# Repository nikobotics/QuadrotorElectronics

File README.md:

# Quadrotor Electronics
Nikobotics Quadcopter Electronics Repository.

Using Altium Designer.

PCBs in this repository include:

- Electronic Flight Computer
- Power Distribution Board
- Peripheral Electronics and Indication Board

Plan to convert schematic into KiCAD upon redesign.

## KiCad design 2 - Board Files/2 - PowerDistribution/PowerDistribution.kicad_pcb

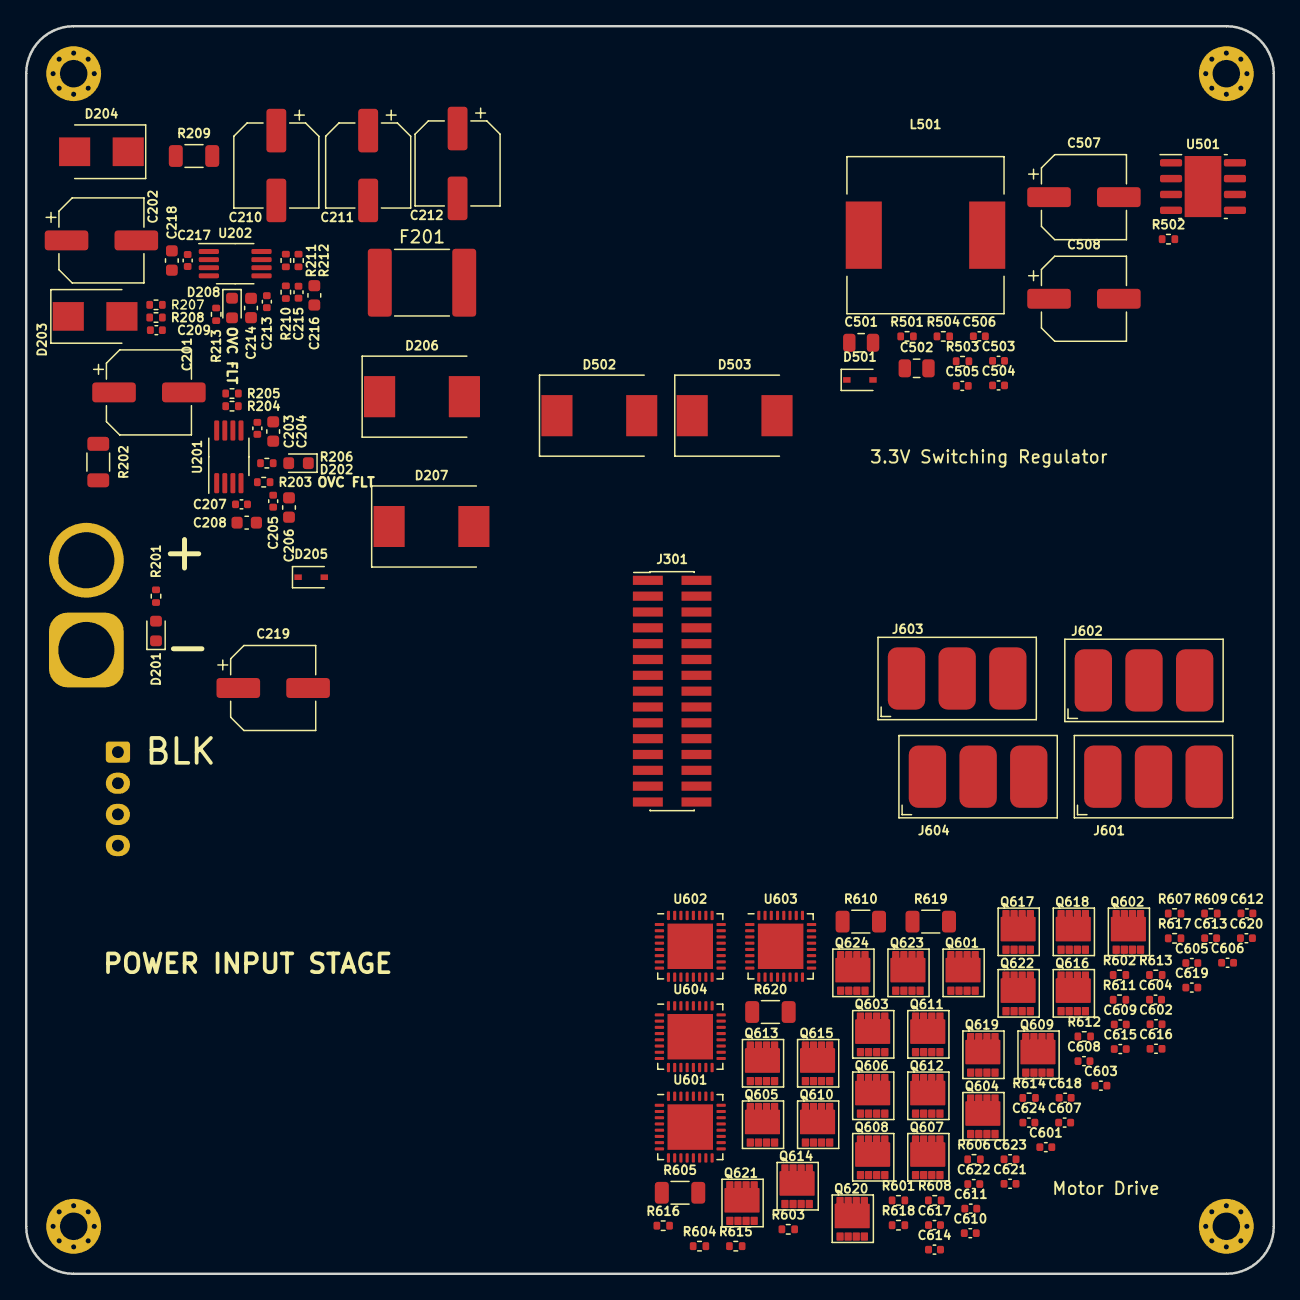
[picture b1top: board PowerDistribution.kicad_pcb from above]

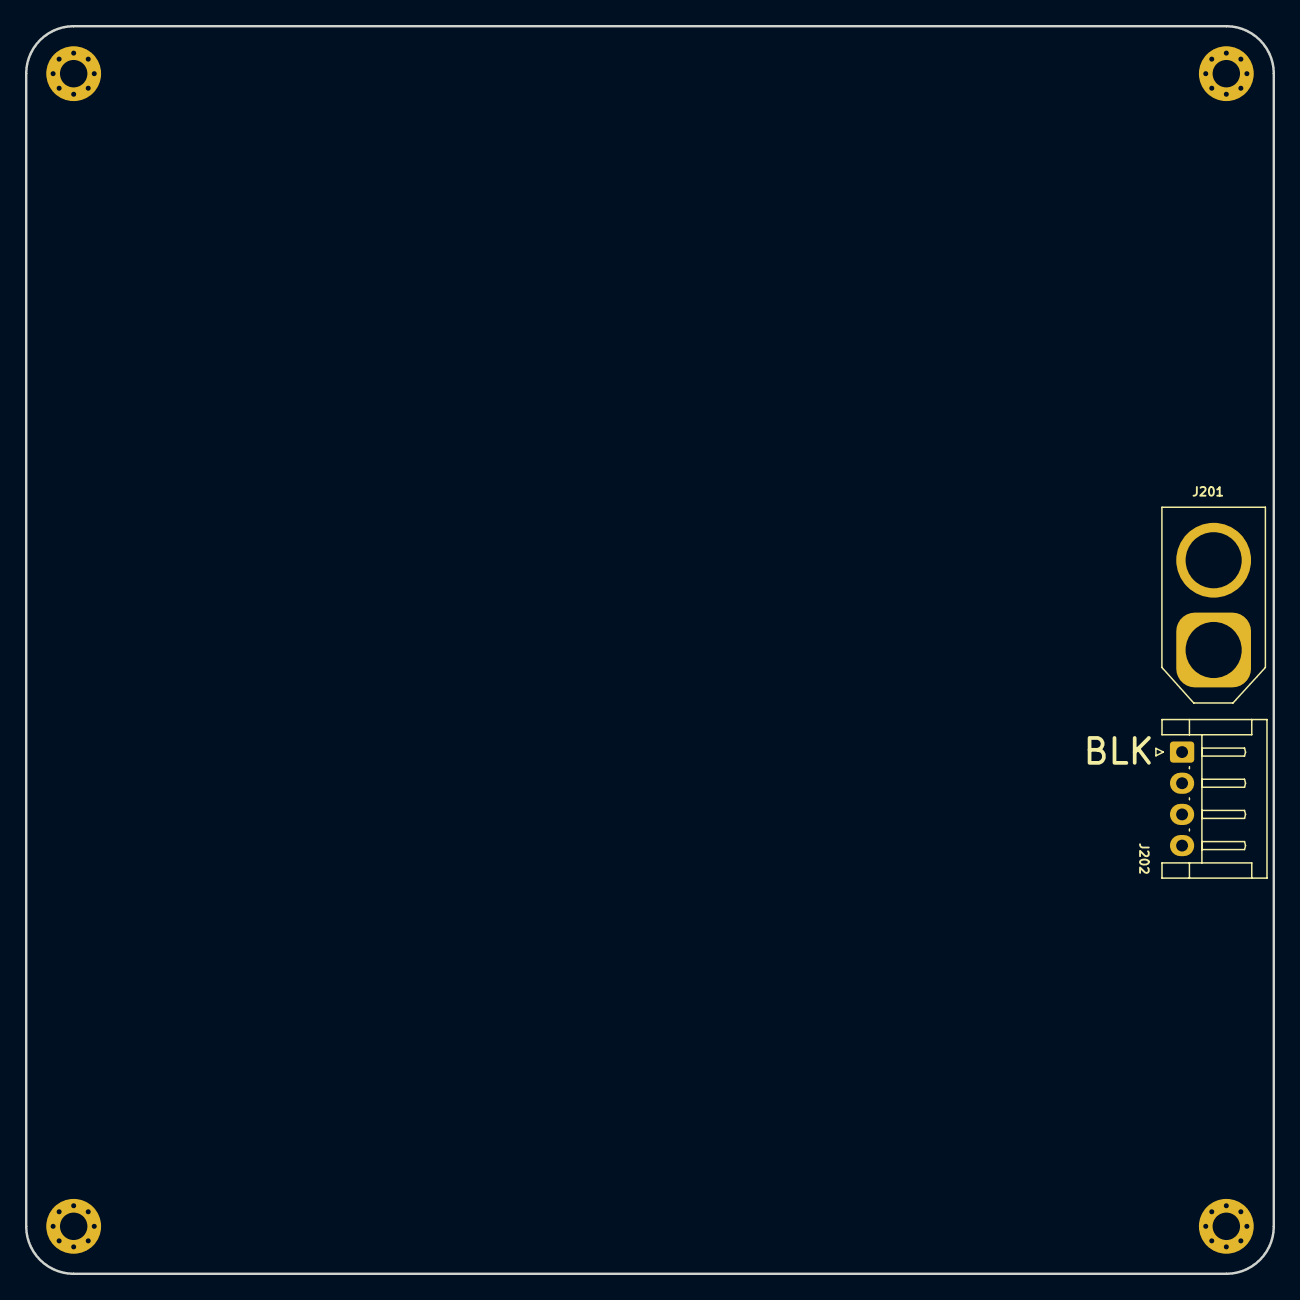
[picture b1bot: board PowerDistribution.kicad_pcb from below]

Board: 6 copper layers, 100.1 x 100.1 mm, 143 parts (2 on the bottom side), 99 nets, no tracks yet.

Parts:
C201, C202, C210, C211, C212, C507, C508: 10u; CP_Elec_6.3x5.4
C203, C205, C207, C213, C215, C217, C505: 10n; C_0402_1005Metric
C204, C206, C208, C214, C216, C218: 1u; C_0603_1608Metric
C209: 100n; C_0402_1005Metric
C219: 47u; CP_Elec_6.3x5.4
C501: 1u; C_0805_2012Metric
C502: 4u2; C_0805_2012Metric
C503, C504, C506, C601, C602, C603, C604, C605, C606, C607, C608, C609, C610, C611, C612, C613, C614, C615, C616, C617, C618, C619, C620, C621, C622, C623, C624: 0u1; C_0402_1005Metric
D201, D202, D208: LED; LED_0603_1608Metric
D203, D204: D; D_SMB
D205, D501: D_Zener; D_SOD-323
D206, D207: D_TVS; D_SMC
D502, D503: D; D_SMC
F201: Polyfuse; Fuse_2920_7451Metric
H101, H102, H103, H104: MountingHole; MountingHole_2.2mm_M2_Pad_Via
J201: Battery Input; AMASS_XT60-F_1x02_P7.20mm_Vertical
J202: Battery Balance Connector; JST_EH_S4B-EH_1x04_P2.50mm_Horizontal
J301: Conn_02x15_Counter_Clockwise; PinHeader_2x15_P1.27mm_Vertical_SMD
J601, J602, J603, J604: Conn_01x03_Female; MotorOutputPads
L501: 3u3; L_12x12mm_H4.5mm
Q601, Q602, Q603, Q604, Q605, Q606, Q607, Q608, Q609, Q610, Q611, Q612, Q613, Q614, Q615, Q616, Q617, Q618, Q619, Q620, Q621, Q622, Q623, Q624: Q_NMOS_GDS; 8-PowerVDFN
R201: R_Small_US; R_0402_1005Metric
R202, R605, R610, R619, R620: 1m, 3W; R_1206_3216Metric
R203, R210: 150R; R_0402_1005Metric
R204: 6k8; R_0402_1005Metric
R205: 3k3; R_0402_1005Metric
R206, R211, R213: 1k2; R_0402_1005Metric
R207: 22k; R_0402_1005Metric
R208: 82k; R_0402_1005Metric
R209: 22m, 3W; R_1206_3216Metric
R212: 9k1; R_0402_1005Metric
R501, R502: 1k; R_0402_1005Metric
R503: 68k1; R_0402_1005Metric
R504: 15k; R_0402_1005Metric
R601, R602, R603, R604, R606, R607, R608, R609, R611, R612, R613, R614, R615, R616, R617, R618: 4k7; R_0402_1005Metric
U201, U202: MAX40056F; MSOP-8_3x3mm_P0.65mm
U501: AOZ6605PI; SOIC-8-1EP_3.9x4.9mm_P1.27mm_EP2.95x4.9mm_Mask2.71x3.4mm
U601, U602, U603, U604: BD63003MUV; QFN-32-1EP_5x5mm_P0.5mm_EP3.65x3.65mm

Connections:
+3.3V: C507.1, C508.1, D501.1 (K), L501.2, R503.1
+3V3: C207.1, C208.1, C217.1, C218.1, R206.2, R213.2, U201.3 (VDD), U202.3 (VDD)
+BATT: C201.1, C202.1, C219.1, C601.1, C602.1, C604.1, C605.1, C606.1, C607.1, C608.1, C609.1, C610.1, C611.1, C613.1, C614.1, C615.1, C616.1, C617.1, C618.1, C619.1, C620.1, C622.1, C623.1, F201.1, Q601.2 (D), Q603.2 (D), Q605.2 (D), Q607.2 (D), Q609.2 (D), Q611.2 (D), Q613.2 (D), Q614.2 (D), Q617.2 (D), Q618.2 (D), Q621.2 (D), Q622.2 (D), R202.2, R603.1, R608.1, R613.1, R616.1, U201.1 (RS+), U601.4 (BRKB), U601.32 (VCC), U602.4 (BRKB), U602.32 (VCC), U603.4 (BRKB), U603.32 (VCC), U604.4 (BRKB), U604.32 (VCC)
/BATT_I_MON: C205.1, C206.1, R203.2
/BATT_V_MON: C209.1, D205.1 (K), R207.1, R208.2
/BatteryInput/BAT+_IN: J201.2, R201.2, R202.1, U201.8 (RS-)
/BatteryInput/BATT_SNS_CIP: R204.2, R205.1, U201.7 (CIP)
/BatteryInput/BATT_SNS_OUT: R203.1, U201.4 (OUT)
/BatteryInput/BATT_SNS_REF: C203.1, C204.1, R204.1, U201.5 (REF)
/BatteryInput/VDC_SNS_CIP: R211.2, R212.1, U202.7 (CIP)
/BatteryInput/VDC_SNS_IN: D204.1 (K), R209.1, U202.8 (RS-)
/BatteryInput/VDC_SNS_OUT: R210.1, U202.4 (OUT)
/BatteryInput/VDC_SNS_REF: C213.1, C214.1, R211.1, U202.5 (REF)
/ControlPower/SWITCH_SRC: C501.1, C502.1, D502.1 (K), D503.1 (K), U501.2 (EN), U501.3 (VIN)
/VDC_I_MON: C215.1, C216.1, R210.2
GND: C201.2, C202.2, C203.2, C204.2, C205.2, C206.2, C207.2, C208.2, C209.2, C210.2, C211.2, C212.2, C213.2, C214.2, C215.2, C216.2, C217.2, C218.2, C219.2, C501.2, C502.2, C503.2, C504.2, C505.2, C507.2, C508.2, C601.2, C604.2, C605.2, C606.2, C607.2, C608.2, C609.2, C610.2, C613.2, C614.2, C615.2, C616.2, C617.2, C618.2, C619.2, C622.2, D201.1 (K), D203.2 (A), D205.2 (A), D206.1 (A1), D207.1 (A1), D501.2 (A), J201.1, J202.1, R205.2, R208.1, R212.2, R504.2, R601.2, R602.2, R604.2, R605.1, R606.2, R607.2, R609.2, R610.1, R611.2, R612.2, R614.2, R615.2, R617.2, R618.2, R619.1, R620.1, U201.6 (GND), U202.6 (GND), U501.4 (GND), U601.3 (CW), U601.7 (GND), U601.18 (RCLS), U601.28 (TEST), U601.33 (GND_EP), U602.7 (GND), U602.18 (RCLS), U602.28 (TEST), U602.33 (GND_EP), U603.3 (CW), U603.7 (GND), U603.18 (RCLS), U603.28 (TEST), U603.33 (GND_EP), U604.7 (GND), U604.18 (RCLS), U604.28 (TEST), U604.33 (GND_EP)
unnamed: C503.1, U501.6 (VCC)
unnamed: C504.1, R501.2
unnamed: C505.1, U501.1 (SS)
unnamed: C506.1, L501.1, U501.9 (LX)
unnamed: C506.2, R502.1
unnamed: C602.2, U601.31 (VG)
unnamed: C603.1, U601.29 (CP1)
unnamed: C603.2, U601.30 (CP2)
unnamed: C611.2, U602.31 (VG)
unnamed: C612.1, U602.29 (CP1)
unnamed: C612.2, U602.30 (CP2)
unnamed: C620.2, U603.31 (VG)
unnamed: C621.1, U603.29 (CP1)
unnamed: C621.2, U603.30 (CP2)
unnamed: C623.2, U604.31 (VG)
unnamed: C624.1, U604.29 (CP1)
unnamed: C624.2, U604.30 (CP2)
unnamed: D201.2 (A), R201.1
unnamed: D202.1 (K), U201.2 (COP)
unnamed: D202.2 (A), R206.1
unnamed: D203.1 (K), D204.2 (A), F201.2, R207.2
unnamed: D208.1 (K), U202.2 (COP)
unnamed: D208.2 (A), R213.1
unnamed: Q601.1 (G), U601.10 (UH)
unnamed: J601.1, Q601.3 (S), Q602.2 (D), U601.9 (U)
unnamed: Q602.1 (G), U601.8 (UL)
unnamed: Q602.3 (S), Q604.3 (S), Q606.3 (S), R605.2, U601.17 (RCL)
unnamed: Q603.1 (G), U601.11 (VH)
unnamed: J601.2, Q603.3 (S), Q604.2 (D), U601.12 (V)
unnamed: Q604.1 (G), U601.13 (VL)
unnamed: Q605.1 (G), U601.16 (WH)
unnamed: J601.3, Q605.3 (S), Q606.2 (D), U601.15 (W)
unnamed: Q606.1 (G), U601.14 (WL)
unnamed: Q607.1 (G), U602.10 (UH)
unnamed: J602.1, Q607.3 (S), Q608.2 (D), U602.9 (U)
unnamed: Q608.1 (G), U602.8 (UL)
unnamed: Q608.3 (S), Q610.3 (S), Q612.3 (S), R610.2, U602.17 (RCL)
unnamed: Q609.1 (G), U602.11 (VH)
unnamed: J602.2, Q609.3 (S), Q610.2 (D), U602.12 (V)
unnamed: Q610.1 (G), U602.13 (VL)
unnamed: Q611.1 (G), U602.16 (WH)
unnamed: J602.3, Q611.3 (S), Q612.2 (D), U602.15 (W)
unnamed: Q612.1 (G), U602.14 (WL)
unnamed: Q613.1 (G), U603.10 (UH)
unnamed: J603.1, Q613.3 (S), Q615.2 (D), U603.9 (U)
unnamed: Q614.1 (G), U604.10 (UH)
unnamed: J604.1, Q614.3 (S), Q616.2 (D), U604.9 (U)
unnamed: Q615.1 (G), U603.8 (UL)
unnamed: Q615.3 (S), Q619.3 (S), Q623.3 (S), R619.2, U603.17 (RCL)
unnamed: Q616.1 (G), U604.8 (UL)
unnamed: Q616.3 (S), Q620.3 (S), Q624.3 (S), R620.2, U604.17 (RCL)
unnamed: Q617.1 (G), U603.11 (VH)
unnamed: J603.2, Q617.3 (S), Q619.2 (D), U603.12 (V)
unnamed: Q618.1 (G), U604.11 (VH)
unnamed: J604.2, Q618.3 (S), Q620.2 (D), U604.12 (V)
unnamed: Q619.1 (G), U603.13 (VL)
unnamed: Q620.1 (G), U604.13 (VL)
unnamed: Q621.1 (G), U603.16 (WH)
unnamed: J603.3, Q621.3 (S), Q623.2 (D), U603.15 (W)
unnamed: Q622.1 (G), U604.16 (WH)
unnamed: J604.3, Q622.3 (S), Q624.2 (D), U604.15 (W)
unnamed: Q623.1 (G), U603.14 (WL)
unnamed: Q624.1 (G), U604.14 (WL)
unnamed: R501.1, U501.7 (COMP)
unnamed: R502.2, U501.5 (BST)
unnamed: R503.2, R504.1, U501.8 (FB)
unnamed: R601.1, U601.6 (SEL1)
unnamed: R602.1, U601.27 (SEL2)
unnamed: R603.2, U601.1 (FG)
unnamed: R604.1, U601.5 (IREF)
unnamed: R606.1, U602.6 (SEL1)
unnamed: R607.1, U602.27 (SEL2)
unnamed: R608.2, U602.1 (FG)
unnamed: R609.1, U602.5 (IREF)
unnamed: R611.1, U603.6 (SEL1)
unnamed: R612.1, U603.27 (SEL2)
unnamed: R613.2, U603.1 (FG)
unnamed: R614.1, U604.6 (SEL1)
unnamed: R615.1, U604.27 (SEL2)
unnamed: R616.2, U604.1 (FG)
unnamed: R617.1, U603.5 (IREF)
unnamed: R618.1, U604.5 (IREF)
VDC: C210.1, C211.1, C212.1, D206.2 (A2), D207.2 (A2), D502.2 (A), R209.2, U202.1 (RS+)

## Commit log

2019-04-10 Added board from previous project
2019-04-10 Added new, blank files and TODO
2019-04-11 Adjusted IMU schematic
2019-04-12 Checked off various to-dos
2019-04-13 Added todo items and CAD for parts
2019-04-13 Added more TODO
2019-04-15 Working on peripheral board
2019-04-15 Working on board heirarchy
2019-04-16 Just need ground net routed on peripheral PCB
2019-04-17 Done with peripheral board as far as I know
2019-05-06 Working on board shaping
2019-06-15 Working on Debug Probe
2019-06-19 Finishing BMP
2019-06-19 Added unsaved files from prev commit:
2019-06-21 Done with Black Magic Probe (not footprints)
2019-06-22 Continuing work
2019-06-24 Finished Auxilliary MCU schematic.
2019-06-24 Fixing minor bugs
2019-07-01 Last commit before switching branches
2019-07-01 Removed all files
2019-07-01 Adding back parts in a better way
2019-07-01 Finishing Control Board dependent parts
2019-07-02 Added new files for SCH
2019-07-02 Added PcbLib
2019-07-02 All current parts have schematic symbols
2019-07-02 Nikobotics SchLib done for now
2019-07-02 Working on Motion Sense Circuit
2019-07-02 Done with IMU Schematic
2019-07-02 Almost done with power distro on control
2019-07-02 Done with PDB, working on DBG
2019-07-02 Done with aux CPU and LEDs
2019-07-02 Working on WiFi schematic
2019-07-09 Working
2019-07-10 Almost done with WiFi- need connection now
2019-07-10 Finished WiFi completely
2019-07-10 Working on Flight Computer
2019-07-10 Fixed motionsense bug
2019-07-10 Almost done. Need to configure BLE balun and Flight Computer
2019-07-10 Fixed power interface bug
2019-07-11 Almost done with control schematic
2019-07-11 Done with control schematic
2019-07-12 Finished Peripheral board
2019-07-12 Finalized BOMs. Need to figure a few specific things out still
2019-07-12 Changed project settings
2019-07-12 Removing deprecated files
2020-01-02 Working on PCB files
2021-03-09 Removed previous files
2022-06-28 Reset files
2022-06-29 Initial project files
2022-07-02 Changes to CPRD
2022-07-02 Added requirements to CPRD
2022-07-05 Added KiCAD symbols to gitignore
2022-07-05 Beginning simulations
2022-07-05 Added opamp test simulation
2022-07-13 Continued Opamp Sim
2022-07-22 Added sch and pcb for initial power input stage
2022-07-22 Part values for power input stage
2022-07-23 Added switching regulator
2022-07-23 Switching regulator changes
2022-07-28 Motor drive initial work
2022-07-28 MOSFETs changed
